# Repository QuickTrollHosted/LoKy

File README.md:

Shield: [![CC BY-NC-SA 4.0][cc-by-nc-sa-shield]][cc-by-nc-sa]

This work is licensed under a
[Creative Commons Attribution-NonCommercial-ShareAlike 4.0 International License][cc-by-nc-sa].

[![CC BY-NC-SA 4.0][cc-by-nc-sa-image]][cc-by-nc-sa]

[cc-by-nc-sa]: http://creativecommons.org/licenses/by-nc-sa/4.0/
[cc-by-nc-sa-image]: https://licensebuttons.net/l/by-nc-sa/4.0/88x31.png
[cc-by-nc-sa-shield]: https://img.shields.io/badge/License-CC%20BY--NC--SA%204.0-lightgrey.svg

# LoKy

- LoKy is an Open-source project which creates a LoRaWAN end-device to connect with Linky meter in France. 
- The most recent firmware is V4

This End-device was created by Ferrari Jérôme and Ho Vu Duy Bao for CNRS/UGA/G-INP – G2ELAB

![CNRS-logo][]
![G2elab-logo][]
![UGA-logo][]
![GINP-logo][]

[GINP-logo]: https://www.grenoble-inp.fr/uas/alias1/LOGO/Grenoble+INP+-+%C3%89tablissement+%28couleur%2C+RVB%2C+120px%29.png
[CNRS-logo]: https://www.cnrs.fr/themes/custom/cnrs/logo.svg
[G2elab-logo]: https://g2elab.grenoble-inp.fr/uas/alias31/LOGO/G2Elab-logo.jpg
[UGA-logo]:https://encrypted-tbn0.gstatic.com/images?q=tbn:ANd9GcR1D0TxrJin49KlU9Oo263OgjsanU9vKQZhKJ9LZsMjxxggnCEKO7NDsN-rW6CEXGJbLEE&usqp=CAU

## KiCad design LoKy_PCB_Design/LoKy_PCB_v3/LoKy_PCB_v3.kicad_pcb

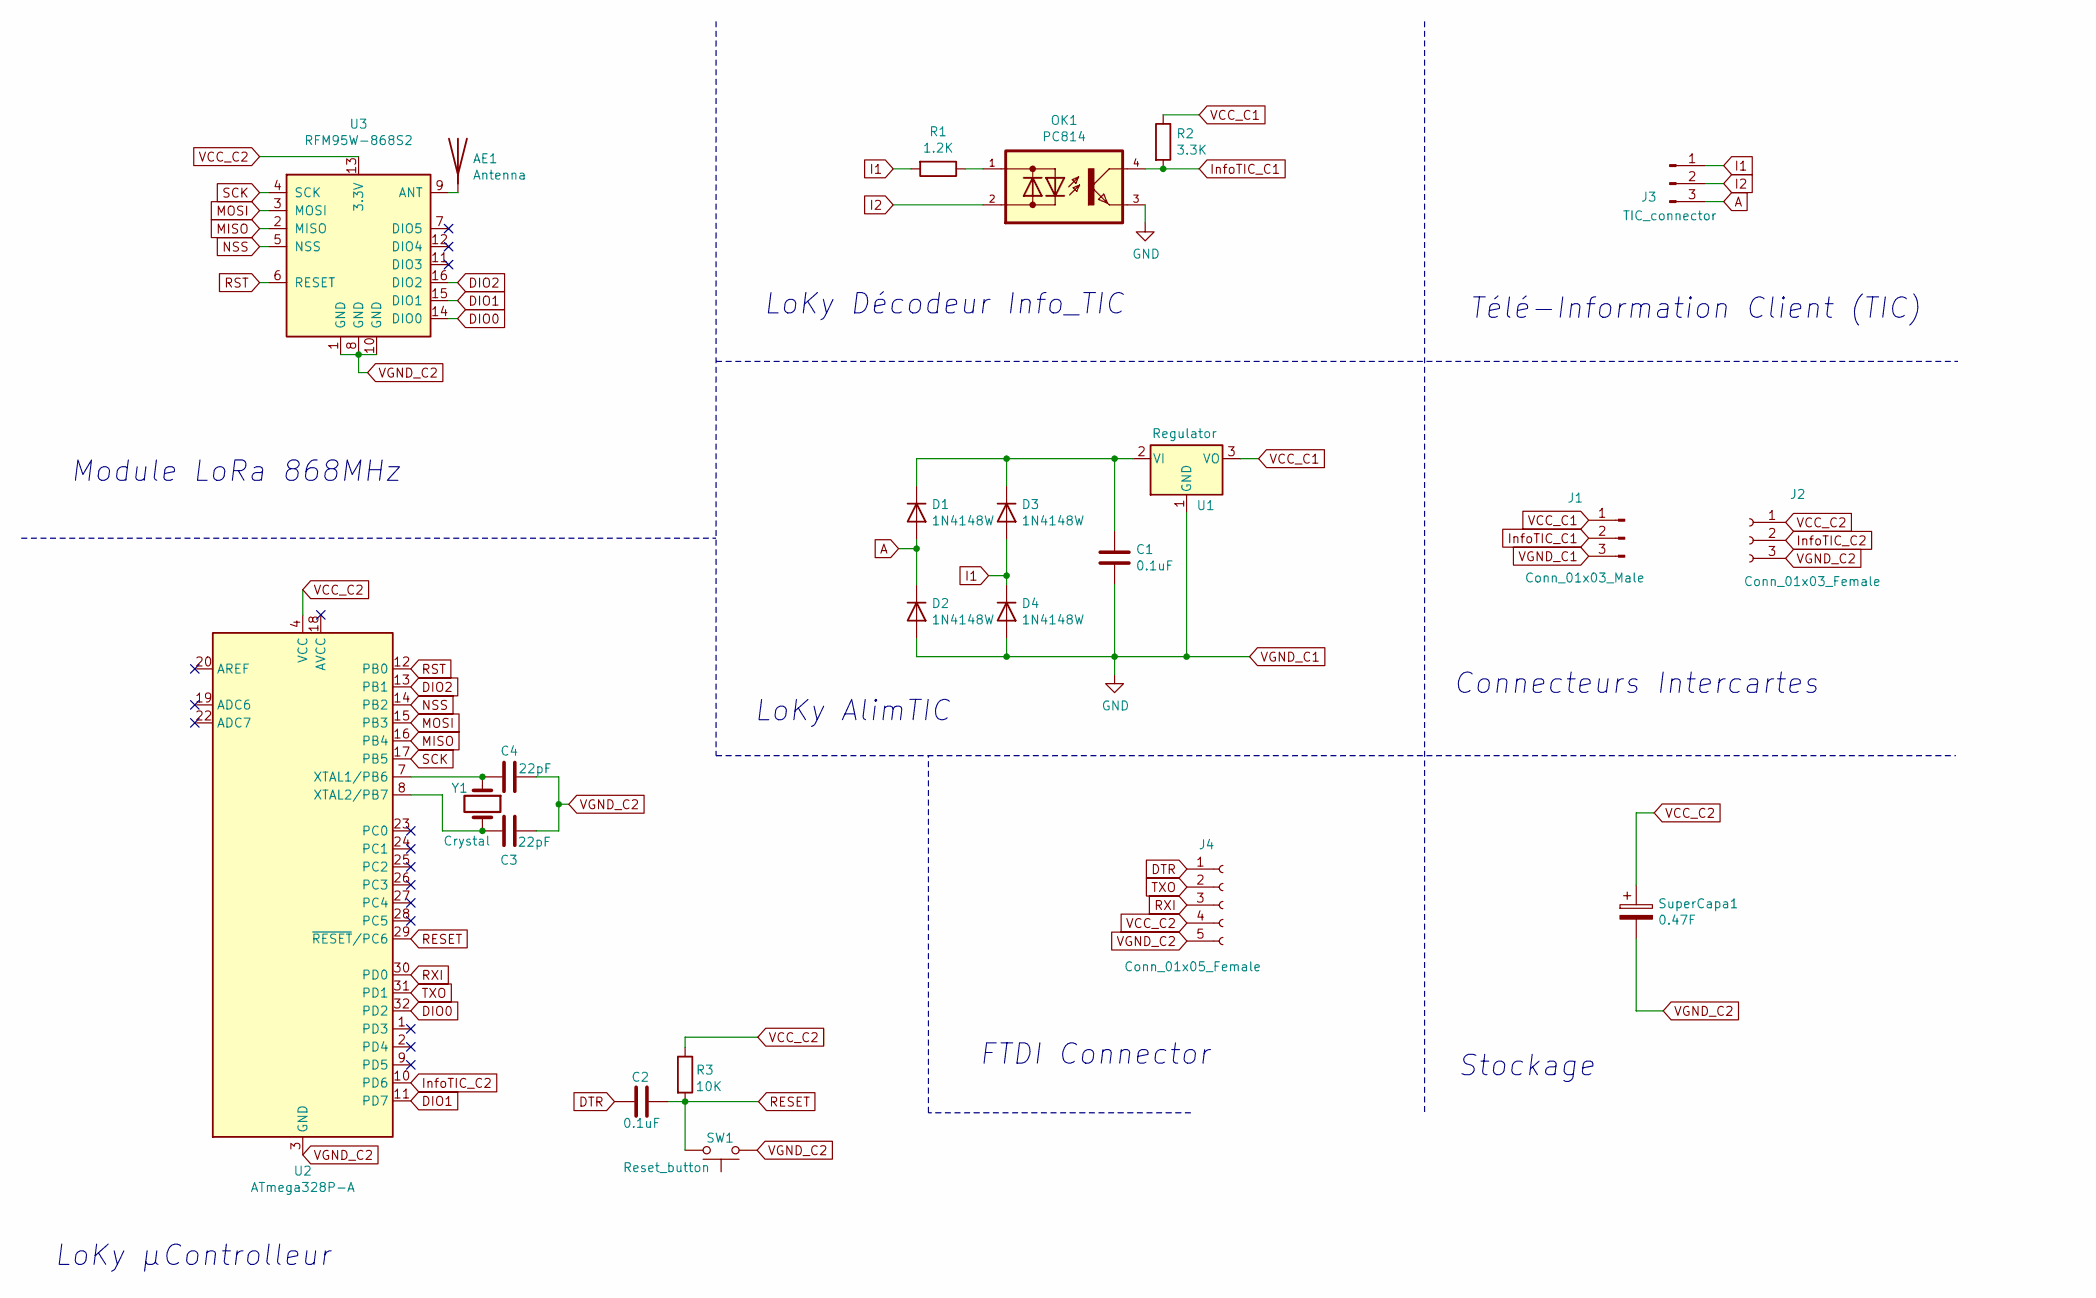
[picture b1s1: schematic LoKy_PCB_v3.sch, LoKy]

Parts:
AE1: Antenna; Texas_SWRA416_868MHz_915MHz
C1: 0.1uF; C_Rect_L7.2mm_W2.5mm_P5.00mm_FKS2_FKP2_MKS2_MKP2
C2: 0.1uF; C_Disc_D4.7mm_W2.5mm_P5.00mm
C3: 22pF; C_Disc_D4.7mm_W2.5mm_P5.00mm
C4: 22pF; C_Rect_L7.2mm_W2.5mm_P5.00mm_FKS2_FKP2_MKS2_MKP2
D1, D2, D3, D4: 1N4148W; D_T-1_P5.08mm_Horizontal
J1: Conn_01x03_Male; PinHeader_1x03_P2.54mm_Horizontal
J2: Conn_01x03_Female; PinSocket_1x03_P2.54mm_Vertical
J3: TIC_connector; Connecteur_Linky
J4: Conn_01x05_Female; PinSocket_1x05_P2.54mm_Vertical
OK1: PC814; DIL04
R1: 1.2K; R_Axial_DIN0207_L6.3mm_D2.5mm_P7.62mm_Horizontal
R2: 3.3K; R_Axial_DIN0207_L6.3mm_D2.5mm_P7.62mm_Horizontal
R3: 10K; R_Axial_DIN0207_L6.3mm_D2.5mm_P7.62mm_Horizontal
SW1: Reset_button; SW_SPST_FSMSM
SuperCapa1: 0.47F; SuperCapa
U1: Regulator; TO-92_Inline
U2: ATmega328P-A; TQFP-32_7x7mm_P0.8mm
U3: RFM95W-868S2; HOPERF_RFM9XW_SMD
Y1: Crystal; Crystal_SMD_HC49-SD

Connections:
A: D1.2 (A), D2.1 (K), J3.3
DIO0: U2.32 (PD2), U3.14 (DIO0)
DIO1: U2.11 (PD7), U3.15 (DIO1)
DIO2: U2.13 (PB1), U3.16 (DIO2)
DTR: C2.1, J4.1
I1: D3.2 (A), D4.1 (K), J3.1, R1.2
I2: J3.2, OK1.2
InfoTIC_C1: J1.2, OK1.4, R2.2
InfoTIC_C2: J2.2, U2.10 (PD6)
MISO: U2.16 (PB4), U3.2 (MISO)
MOSI: U2.15 (PB3), U3.3 (MOSI)
NSS: U2.14 (PB2), U3.5 (NSS)
unnamed: AE1.1, U3.9 (ANT)
unnamed: C1.1, D1.1 (K), D3.1 (K), U1.2 (VI)
unnamed: C3.1, U2.8 (XTAL2/PB7), Y1.2
unnamed: C4.1, U2.7 (XTAL1/PB6), Y1.1
unnamed: OK1.1, R1.1
RESET: C2.2, R3.2, SW1.1, U2.29 (~RESET~/PC6)
RST: U2.12 (PB0), U3.6 (RESET)
RXI: J4.3, U2.30 (PD0)
SCK: U2.17 (PB5), U3.4 (SCK)
TXO: J4.2, U2.31 (PD1)
VCC_C1: J1.1, R2.1, U1.3 (VO)
VCC_C2: J2.1, J4.4, R3.1, SuperCapa1.1, U2.4 (VCC), U2.6 (VCC), U3.13 (3.3V)
VGND_C1: C1.2, D2.2 (A), D4.2 (A), J1.3, OK1.3, U1.1 (GND)
VGND_C2: C3.2, C4.2, J2.3, J4.5, SW1.2, SuperCapa1.2, U2.3 (GND), U2.5 (GND), U2.21 (GND), U3.1 (GND), U3.8 (GND), U3.10 (GND)

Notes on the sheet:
LoKy μControlleur
Module LoRa 868MHz
LoKy AlimTIC
LoKy Décodeur Info_TIC
Télé-Information Client (TIC)
Connecteurs Intercartes
Stockage
FTDI Connector

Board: 2 copper layers, 22 parts (0 on the bottom side), 25 nets, no tracks yet.

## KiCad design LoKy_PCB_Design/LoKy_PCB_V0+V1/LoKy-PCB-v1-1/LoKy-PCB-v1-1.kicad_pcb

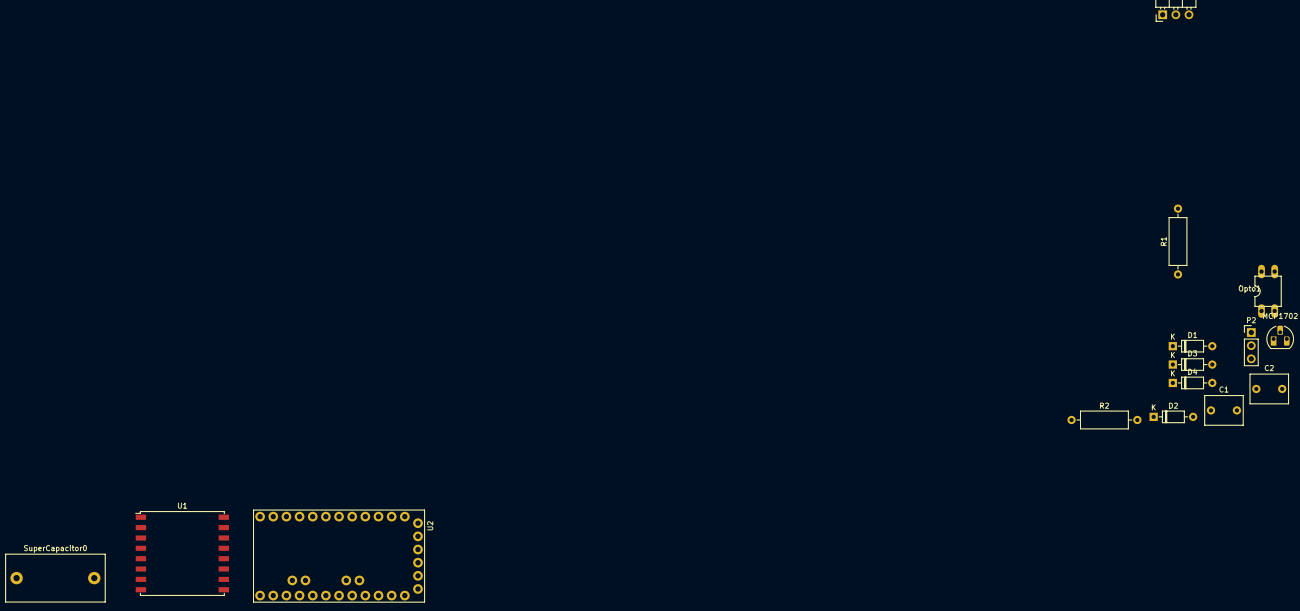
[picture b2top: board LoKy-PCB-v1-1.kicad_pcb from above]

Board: 2 copper layers, 15 parts (0 on the bottom side), 17 nets, no tracks yet.

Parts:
C1, C2: 1uF; C_Rect_L7.2mm_W5.5mm_P5.00mm_FKS2_FKP2_MKS2_MKP2
D1, D2, D3, D4: 1N4148; D_DO-35_SOD27_P7.62mm_Horizontal
MCP1702: MCP1702; TO-92_HandSolder
Opto1: PC814; DIL04
P1: HEADER_M_2.54MM_1R3P_ST_AU_PTH; PinHeader_1x03_P2.54mm_Horizontal
P2: HEADER_M_2.54MM_1R3P_ST_AU_PTH; PinHeader_1x03_P2.54mm_Vertical
R1: 1.2K; R_Axial_DIN0309_L9.0mm_D3.2mm_P12.70mm_Horizontal
R2: 3.3K; R_Axial_DIN0309_L9.0mm_D3.2mm_P12.70mm_Horizontal
SuperCapacitor0: 0.5F; C_Rect_L19.0mm_W9.0mm_P15.00mm_MKS4
U1: RFM95; HOPERF_RFM9XW_SMD
U2: ARDUINO_PRO_MINI; MODULE_ARDUINO_PRO_MINI

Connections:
A: D1.2, D2.1, P1.3
DIO0: U1.14, U2.JP7_8
DIO1: U1.15, U2.JP7_3
DIO2: U1.16, U2.JP7_1
GNDREF: C1.2, C2.2, D2.2, D4.2, MCP1702.1, Opto1.3, P2.3, SuperCapacitor0.2, U1.1, U1.8, U1.10, U2.JP6_2, U2.JP7_9
I1: D3.2, D4.1, P1.1, R1.1
I2: Opto1.2, P1.2
InfoTIC: Opto1.4, P2.2, R2.2, U2.JP7_4
MISO: U1.2, U2.JP6_10
MOSI: U1.3, U2.JP6_11
NSS: U1.5, U2.JP6_12
unnamed: C1.1, D1.1, D3.1, MCP1702.2
unnamed: Opto1.1, R1.2
unnamed: U2.JP1_5, U2.JP1_6
RST: U1.6, U2.JP7_2
SCK: U1.4, U2.JP6_9
Vcc: C2.1, MCP1702.3, P2.1, R2.1, SuperCapacitor0.1, U1.13, U2.JP1_4, U2.JP6_4

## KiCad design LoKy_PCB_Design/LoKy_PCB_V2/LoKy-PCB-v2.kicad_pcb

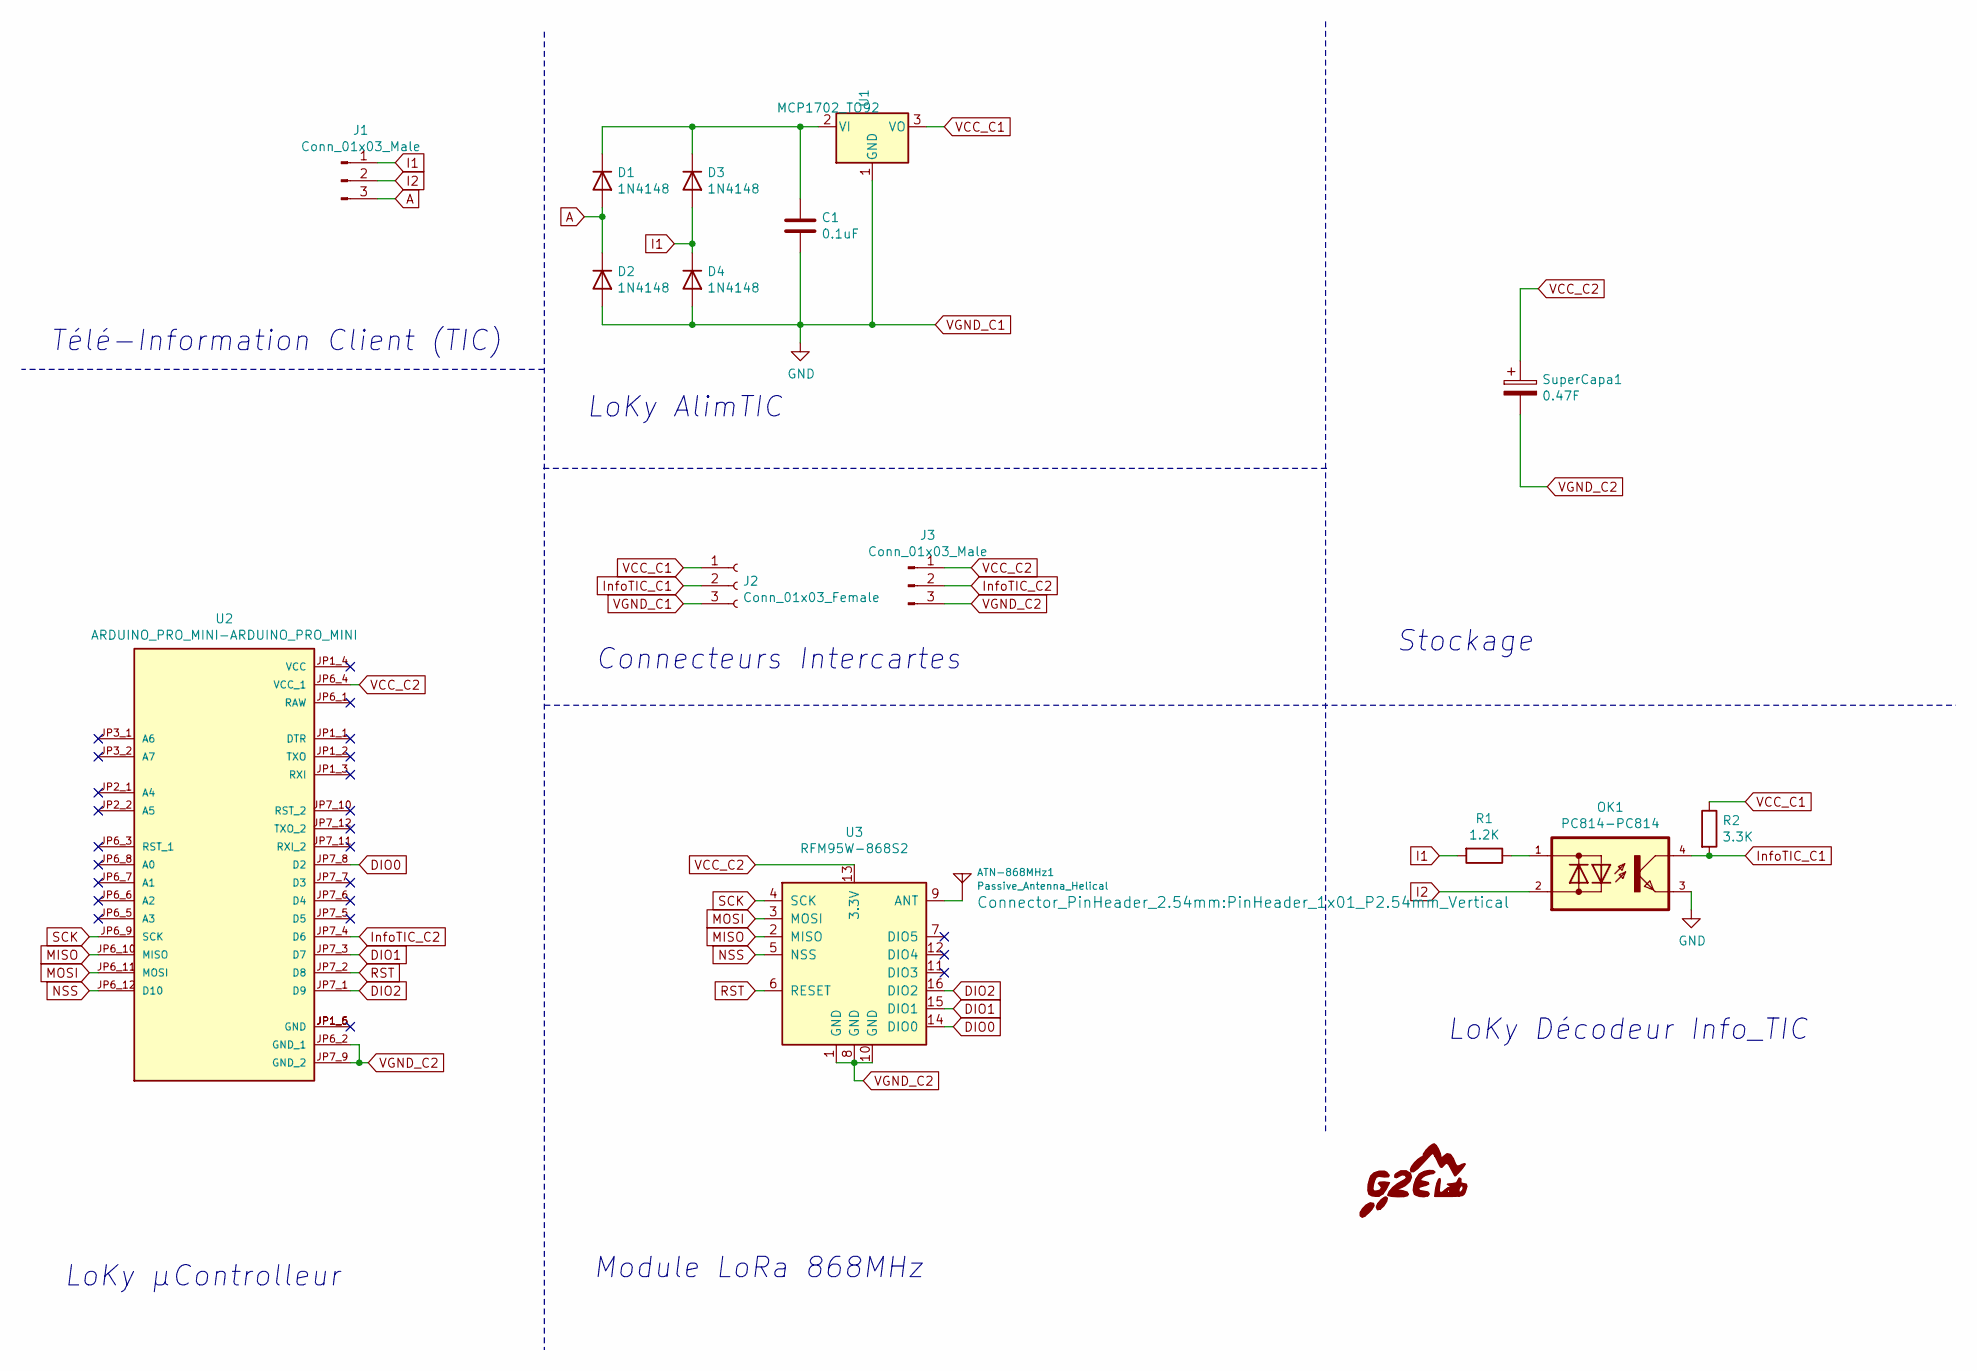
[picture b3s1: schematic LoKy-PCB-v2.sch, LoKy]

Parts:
ATN-868MHz1: Passive_Antenna_Helical; PinHeader_1x01_P2.54mm_Vertical
C1: 0.1uF; C_Rect_L7.0mm_W2.5mm_P5.00mm
D1, D2, D3, D4: 1N4148; D_DO-35_SOD27_P7.62mm_Horizontal
J1: Conn_01x03_Male; Connecteur_Linky
J2: Conn_01x03_Female; PinHeader_1x03_P2.54mm_Vertical
J3: Conn_01x03_Male; PinHeader_1x03_P2.54mm_Vertical
OK1: PC814-PC814; DIL04
R1: 1.2K; R_Axial_DIN0207_L6.3mm_D2.5mm_P7.62mm_Horizontal
R2: 3.3K; R_Axial_DIN0207_L6.3mm_D2.5mm_P7.62mm_Horizontal
SuperCapa1: 0.47F; SuperCapa
U1: MCP1702_TO92; TO-92_Inline
U2: ARDUINO_PRO_MINI-ARDUINO_PRO_MINI; ArduProMini_minimalist; PARTREV N/A
U3: RFM95W-868S2; HOPERF_RFM9XW_SMD

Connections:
A: D1.2 (A), D2.1 (K), J1.3
DIO0: U2.JP7_8 (D2), U3.14 (DIO0)
DIO1: U2.JP7_3 (D7), U3.15 (DIO1)
DIO2: U2.JP7_1 (D9), U3.16 (DIO2)
I1: D3.2 (A), D4.1 (K), J1.1, R1.2
I2: J1.2, OK1.2
InfoTIC_C1: J2.2, OK1.4, R2.2
InfoTIC_C2: J3.2, U2.JP7_4 (D6)
MISO: U2.JP6_10 (MISO), U3.2 (MISO)
MOSI: U2.JP6_11 (MOSI), U3.3 (MOSI)
NSS: U2.JP6_12 (D10), U3.5 (NSS)
unnamed: ATN-868MHz1.1, U3.9 (ANT)
unnamed: C1.1, D1.1 (K), D3.1 (K), U1.2 (VI)
unnamed: OK1.1, R1.1
unnamed: U2.JP1_5 (GND), U2.JP1_6 (GND)
RST: U2.JP7_2 (D8), U3.6 (RESET)
SCK: U2.JP6_9 (SCK), U3.4 (SCK)
VCC_C1: J2.1, R2.1, U1.3 (VO)
VCC_C2: J3.1, SuperCapa1.1, U2.JP6_4 (VCC_1), U3.13 (3.3V)
VGND_C1: C1.2, D2.2 (A), D4.2 (A), J2.3, OK1.3, U1.1 (GND)
VGND_C2: J3.3, SuperCapa1.2, U2.JP6_2 (GND_1), U2.JP7_9 (GND_2), U3.1 (GND), U3.8 (GND), U3.10 (GND)

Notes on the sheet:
LoKy μControlleur
Module LoRa 868MHz
LoKy AlimTIC
LoKy Décodeur Info_TIC
Télé-Information Client (TIC)
Connecteurs Intercartes
Stockage

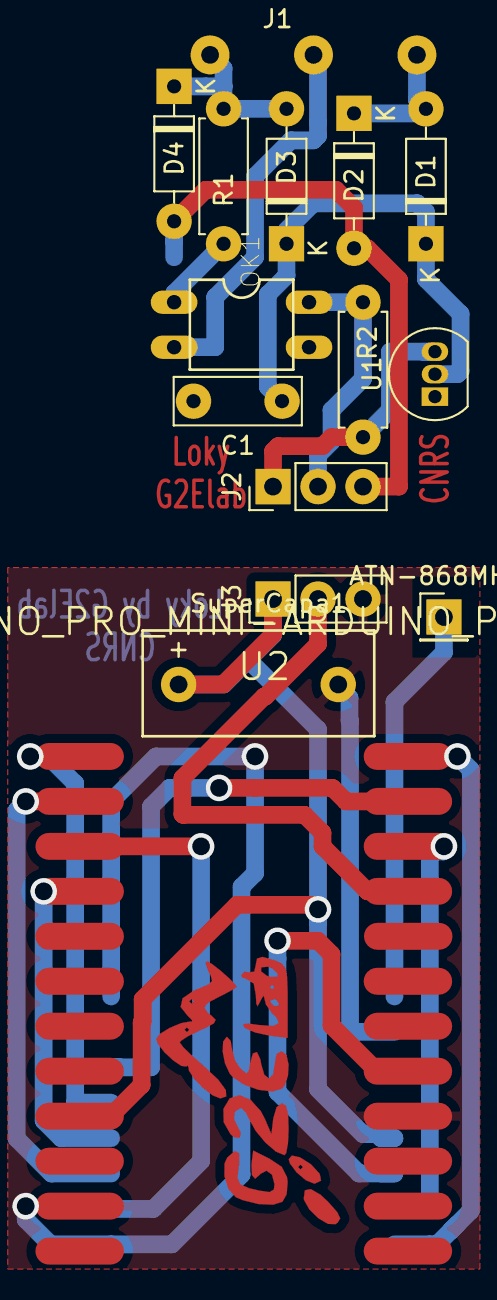
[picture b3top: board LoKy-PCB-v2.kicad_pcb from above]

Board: 2 copper layers, 16 parts (1 on the bottom side), 21 nets.

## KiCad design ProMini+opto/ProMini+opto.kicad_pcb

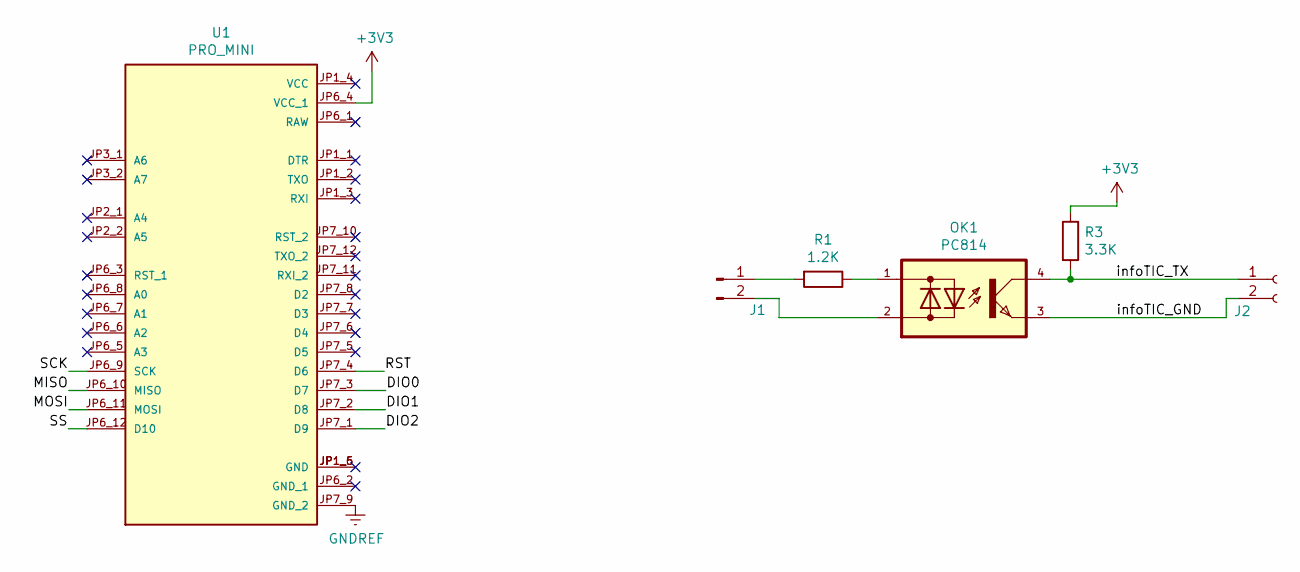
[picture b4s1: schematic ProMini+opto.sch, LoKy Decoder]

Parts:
J1, J2: PinHeader_1x02_P2.54mm_Vertical
OK1: PC814; DIL04
R1: 1.2K; R_Axial_DIN0204_L3.6mm_D1.6mm_P5.08mm_Horizontal
R3: 3.3K; R_Axial_DIN0204_L3.6mm_D1.6mm_P5.08mm_Horizontal
U1: PRO_MINI; MODULE_ARDUINO_PRO_MINI; PARTREV N/A

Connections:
+3V3: R3.1, U1.JP6_4 (VCC_1)
/DIO0: U1.JP7_3 (D7)
/DIO1: U1.JP7_2 (D8)
/DIO2: U1.JP7_1 (D9)
/MISO: U1.JP6_10 (MISO)
/MOSI: U1.JP6_11 (MOSI)
/RST: U1.JP7_4 (D6)
/SCK: U1.JP6_9 (SCK)
/SS: U1.JP6_12 (D10)
/infoTIC_GND: J2.2, OK1.3
/infoTIC_TX: J2.1, OK1.4, R3.2
GNDREF: U1.JP7_9 (GND_2)
unnamed: J1.1, R1.2
unnamed: J1.2, OK1.2
unnamed: OK1.1, R1.1
unnamed: U1.JP1_5 (GND), U1.JP1_6 (GND)

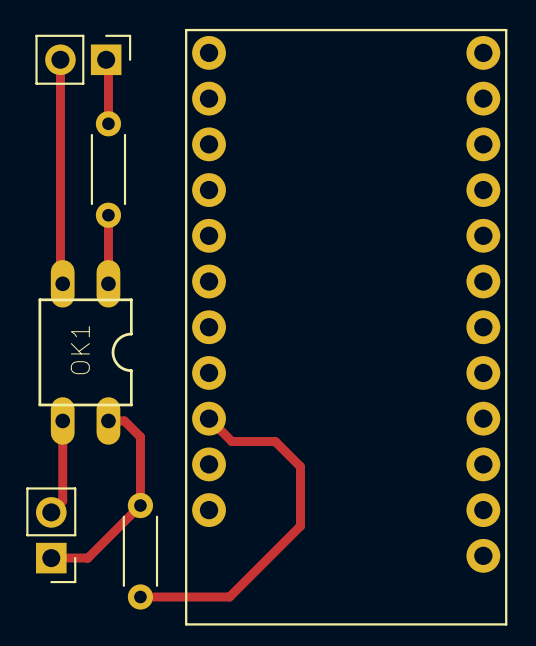
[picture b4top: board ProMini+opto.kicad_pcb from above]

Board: 2 copper layers, 6 parts (0 on the bottom side), 7 nets.

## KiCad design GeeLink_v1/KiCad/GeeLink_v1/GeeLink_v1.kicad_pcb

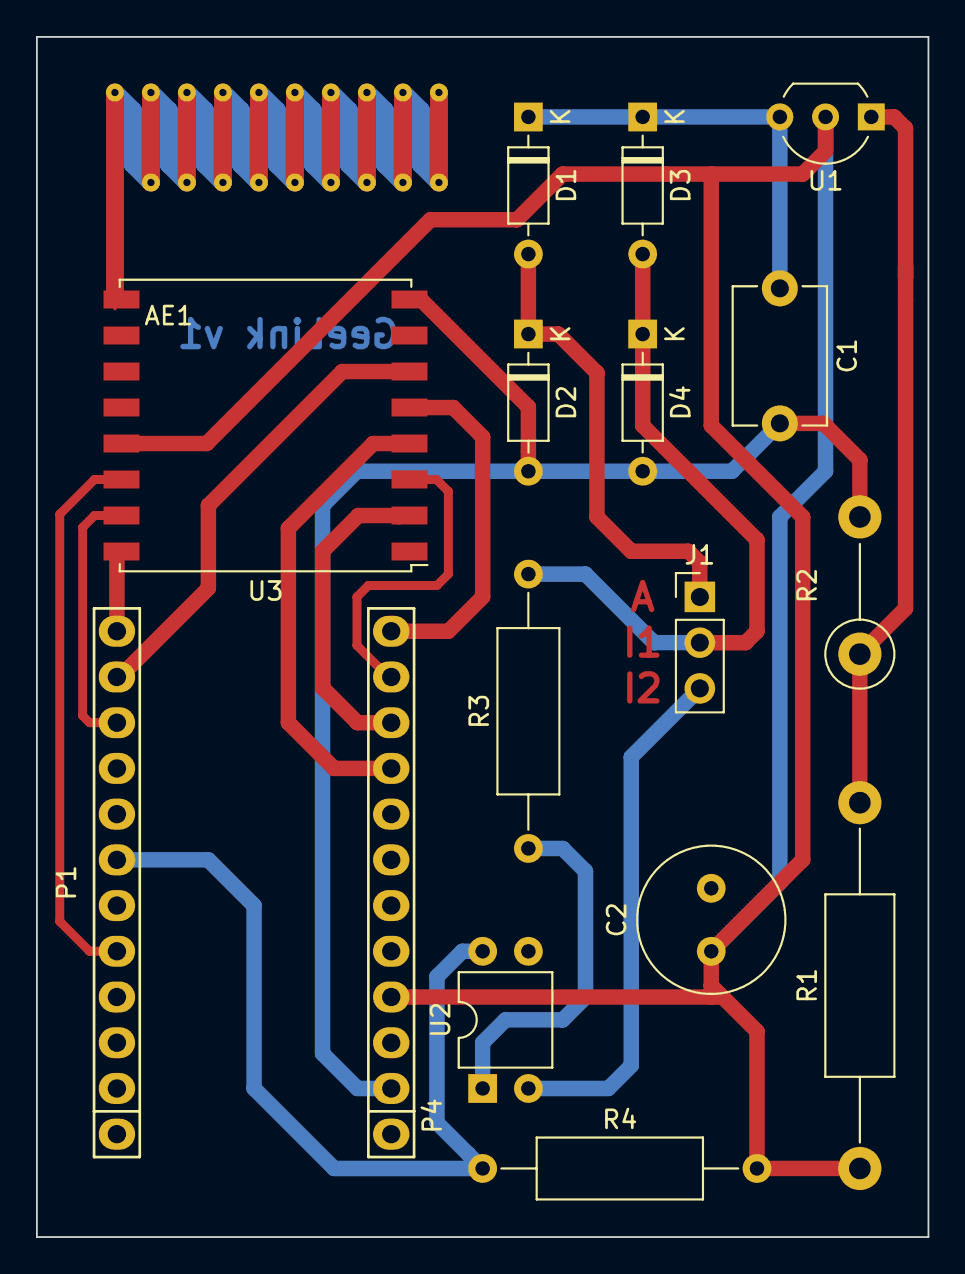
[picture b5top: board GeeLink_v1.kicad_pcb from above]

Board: 2 copper layers, 49.5 x 66.7 mm, 17 parts (0 on the bottom side), 18 nets.

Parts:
AE1: Antenna; Texas_SWRA416_868MHz_915MHz
C1: 1µF; C_Disc_D7.5mm_W5.0mm_P7.50mm
C2: C_Adj; C_Radial_D8.0mm_H7.0mm_P3.50mm
D1, D2, D3, D4: 1N4148; D_DO-35_SOD27_P7.62mm_Horizontal
J1: TIC; PinHeader_1x03_P2.54mm_Vertical
P1: Digital; Socket_Strip_Arduino_1x12
P4: Analog; Socket_Strip_Arduino_1x12
R1: 240; R_Axial_DIN0411_L9.9mm_D3.6mm_P20.32mm_Horizontal
R2: R_Adj; R_Axial_DIN0411_L9.9mm_D3.6mm_P7.62mm_Vertical
R3: 1,2K; R_Axial_DIN0309_L9.0mm_D3.2mm_P15.24mm_Horizontal
R4: 3.3K; R_Axial_DIN0309_L9.0mm_D3.2mm_P15.24mm_Horizontal
U1: LM317; TO-92_Inline_Wide
U2: PC814; DIP-4_W7.62mm
U3: RFM95W-868S2; HOPERF_RFM9XW_SMD

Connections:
/ANT: AE1.1, U3.9
/DI00: P1.5, U3.14
/DI01: P1.10, U3.15
/DI02: P1.12, U3.16
/MISO: P4.10, U3.2
/MOSI: P4.11, U3.3
/NSS: P4.12, U3.5
/RESET: P1.11, U3.6
/SCK: P4.9, U3.4
A: D1.2, D2.1, J1.1
GND: C1.2, C2.2, D2.2, D4.2, P1.4, P4.2, R2.2, U2.3, U3.8
I1: D3.2, D4.1, J1.2, R3.2
I2: J1.3, U2.2
unnamed: C1.1, D1.1, D3.1, U1.3
unnamed: R1.2, R2.1, U1.1
unnamed: R3.1, U2.1
RX: P1.7, R4.1, U2.4
VCC: C2.1, P4.4, R1.1, R4.2, U1.2, U3.13

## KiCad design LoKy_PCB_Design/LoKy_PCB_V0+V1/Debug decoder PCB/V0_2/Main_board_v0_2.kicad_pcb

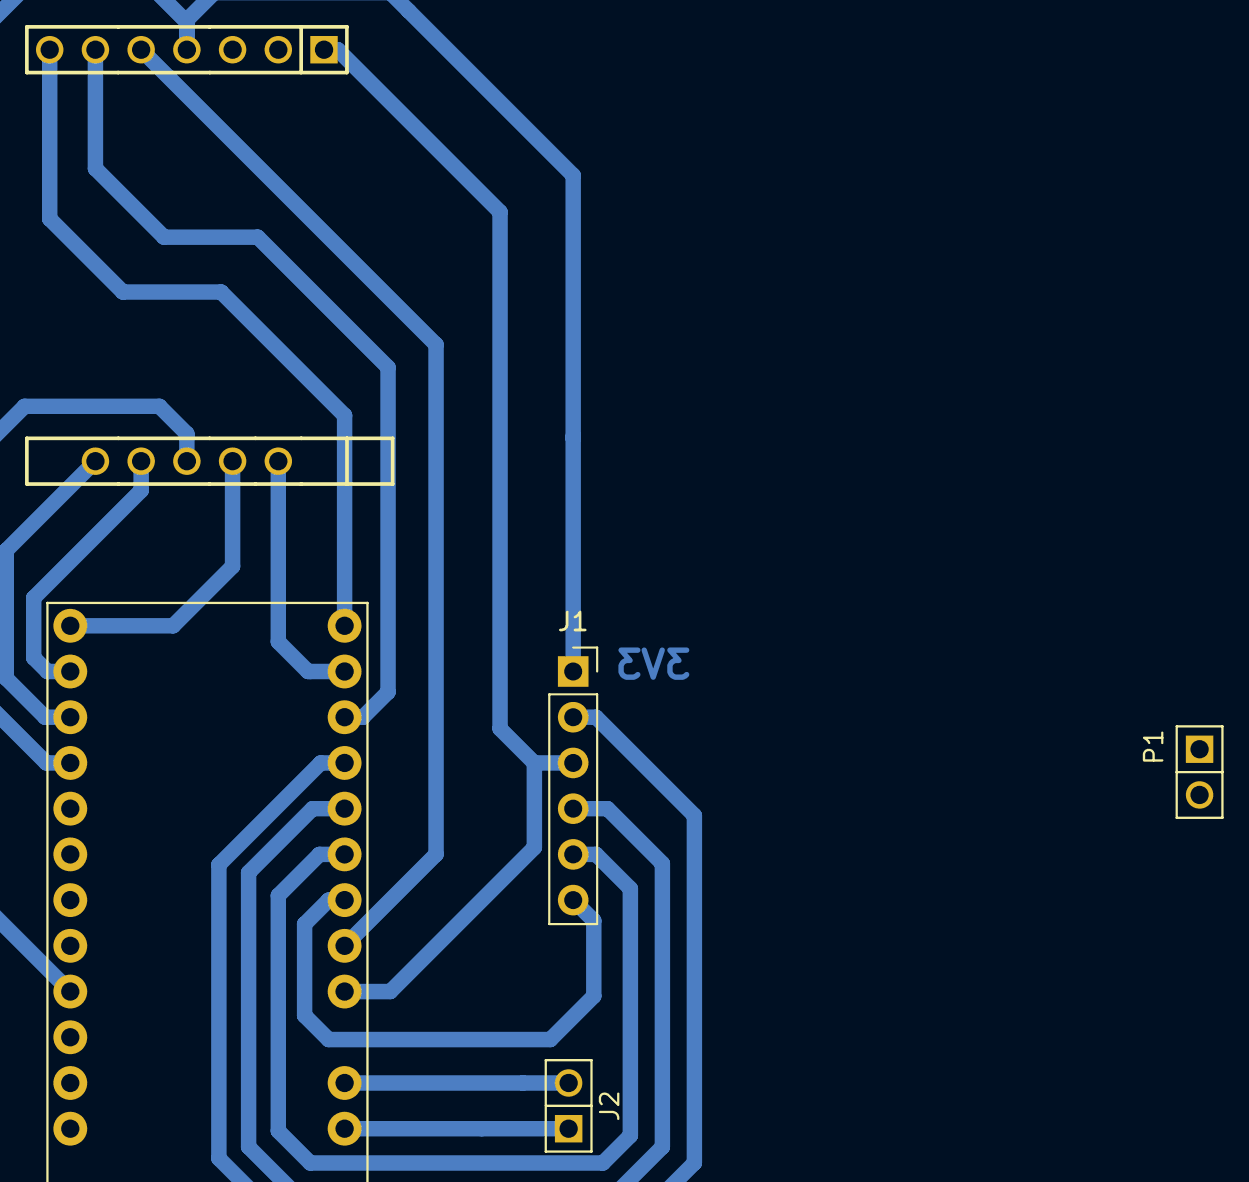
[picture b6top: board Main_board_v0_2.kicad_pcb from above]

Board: 2 copper layers, 6 parts (0 on the bottom side), 17 nets.

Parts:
J1: H1; PinSocket_1x06_P2.54mm_Vertical
J2: H2; HEADER_F_2.54MM_1R2P_ST_AU_PTH
P1: HEADER_M_2.54MM_1R2P_ST_AU_PTH
P1#2: H1; HEADER_M_2.54MM_1R7P_ST_AU_PTH
P2: H2; HEADER_M_2.54MM_1R8P_ST_AU_PTH
U1: ARDUINO_PRO_MINI; MODULE_ARDUINO_PRO_MINI

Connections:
/3V3: J1.1, P1#2.4, U1.JP6_4
/D3: J1.6, U1.JP7_7
/D4: J1.5, U1.JP7_6
/D5: J1.4, U1.JP7_5
/D6: J1.2, U1.JP7_4
/DIO0: P1#2.5, U1.JP7_8
/DIO1: P1#2.6, U1.JP7_3
/DIO2: P1#2.7, U1.JP7_1
/GND: J1.3, P1#2.1, U1.JP7_9
/MISO: P2.7, U1.JP6_10
/MOSI: P2.6, U1.JP6_11
/NSS: P2.4, U1.JP6_12
/RST: P2.3, U1.JP7_2
/SCK: P2.5, U1.JP6_9
unnamed: J2.1, U1.JP7_12
unnamed: J2.2, U1.JP7_11
unnamed: U1.JP1_5, U1.JP1_6

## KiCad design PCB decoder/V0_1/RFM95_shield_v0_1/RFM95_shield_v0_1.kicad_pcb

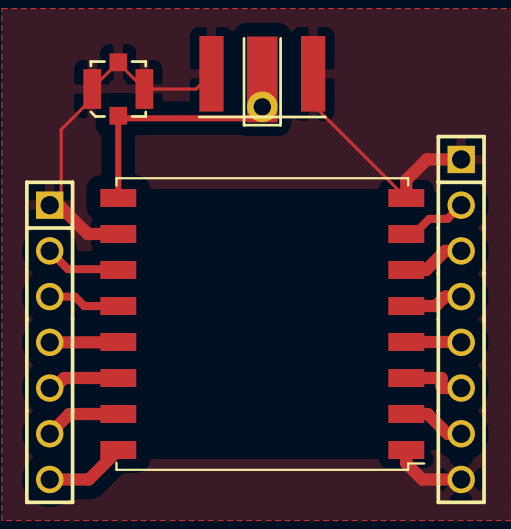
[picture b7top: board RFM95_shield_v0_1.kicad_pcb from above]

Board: 2 copper layers, 6 parts (0 on the bottom side), 13 nets.

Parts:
AE1: Antenna_Helical_RA; ANTENNA_HELICAL_RA
J1: u.FL; U.FL-R-SMT
J2: SMA; SMA_EDGE
P1: H1; HEADER_M_2.54MM_1R7P_ST_AU_PTH
P2: H2; HEADER_M_2.54MM_1R8P_ST_AU_PTH
U1: RFM95; HOPERF_RFM9XW_SMD

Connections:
/3V3: P1.4, U1.13
/DIO0: P1.5, U1.14
/DIO1: P1.6, U1.15
/DIO2: P1.7, U1.16
/GND: J1.2, J1.3, J1.4, J2.2, J2.3, P1.1, P2.1, P2.8, U1.1, U1.8, U1.10
/MISO: P2.7, U1.2
/MOSI: P2.6, U1.3
/NSS: P2.4, U1.5
/RST: P2.3, U1.6
/SCK: P2.5, U1.4
unnamed: P1.2, U1.11
unnamed: P1.3, U1.12
unnamed: P2.2, U1.7

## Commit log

2021-02-01 Inherit from GeeLink
    Useful docs from GeeLink
2021-02-01 Update documents
2021-02-01 Update document and LoKy decoder
2021-02-03 Upload KiCad design v1
2021-02-09 Publish PCB design for LoKy decoder v0.1
2021-02-10 Update new design
2021-02-11 Separate each element
2021-02-17 PCB decoder v0 update
2021-02-17 Update 17/02/2021
2021-02-24 Test Fevrier 24
2021-03-10 Update 10-March-2021
2021-03-17 Small Update for Node-2
2021-03-17 Update Test Option Tarifaire BASE
2021-03-18 Remove test-0 BASE
2021-03-18 Update test MARS-18 for option BASE
2021-03-19 Remove Template, Add HCHP + BASE
2021-03-28 Add files via upload
    Modification of Dimensions
2021-04-01 Update PCB version 1
2021-04-02 Update KiCAD library
2021-04-09 Modification to fit with linky
2021-04-09 Update to fit with linky
2021-04-09 Update the PCB to revision 2
2021-04-09 Clean of repository
2021-04-09 Update of librairies
2021-04-09 Move folder LoKy-PCB-v2.pretty
2021-04-09 Reamenagement of folder to main items (Code,PCB,Documentation,STL)
2021-04-09 Modification of naming to LoKy
2021-04-09 Update Tutorial + Folder Name modification
2021-04-10 Clean firmware
2021-04-10 Update LoKy Tutorial
2021-04-14 Update LoKy template v1
2021-05-27 Update migration to TTI v3
2021-06-04 Update 04-Juin
2021-06-07 Update LoKy v2 - Auto reset
2021-06-08 V2 du boitier
    V2 du boitier
2021-06-08 Ajout bouton reset
2021-06-08 Reorientation corps pour impression directe
2021-06-08 Correction lettre sur couvercle pour impression 3D
    Correction lettre sur couvercle pour impression 3D
2021-06-09 V3 du boitier
    Ajout d'un passe fil pour permettre l'ajout d'un autre capteur en parallèle
2021-06-13 V3
    Modification to hold board
2021-06-16 LoKy firmware v2.1 update
2021-07-13 Update Test 7 LoKys
2021-07-20 Update 1_OPTARIF
2021-07-20 Update LoKy_decoder_v2 on TTN
2021-07-20 Rearrange Folders
2021-07-20 LoKy firmware v2.3
    Update firmware version 2.2 to adapt with payload formatter v2 on TTNv3
2021-07-20 V4
    V4
2021-07-21 Correction of HCHP/BASE option
    Correction of HCHP/BASE option
2021-07-25 Update Node chez Fred
2021-07-28 Update LICENSE
2021-07-28 Add new directory
2021-07-28 Upload New File
